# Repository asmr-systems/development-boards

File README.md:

# development-boards
development boards

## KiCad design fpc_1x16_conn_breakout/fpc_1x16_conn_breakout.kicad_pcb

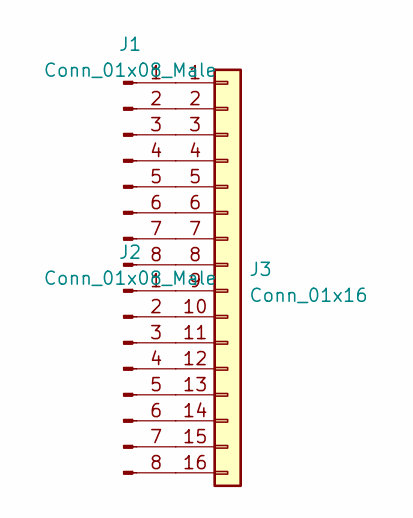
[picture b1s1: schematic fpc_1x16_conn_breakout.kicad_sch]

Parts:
J1, J2: Conn_01x08_Male; PinHeader_1x08_P2.54mm_Vertical
J3: Conn_01x16; Conn_FFC_1x16_0.5mm_TE_117347426

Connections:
unnamed: J1.1, J3.1
unnamed: J1.2, J3.2
unnamed: J1.3, J3.3
unnamed: J1.4, J3.4
unnamed: J1.5, J3.5
unnamed: J1.6, J3.6
unnamed: J1.7, J3.7
unnamed: J1.8, J3.8
unnamed: J2.1, J3.9
unnamed: J2.2, J3.10
unnamed: J2.3, J3.11
unnamed: J2.4, J3.12
unnamed: J2.5, J3.13
unnamed: J2.6, J3.14
unnamed: J2.7, J3.15
unnamed: J2.8, J3.16

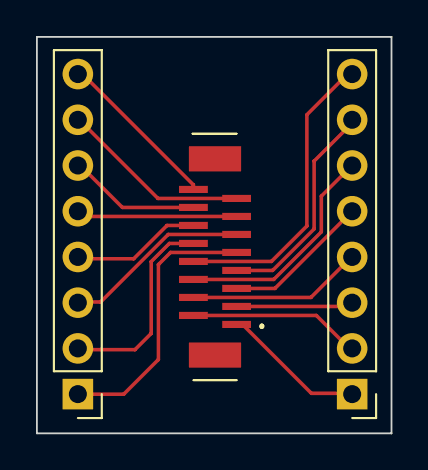
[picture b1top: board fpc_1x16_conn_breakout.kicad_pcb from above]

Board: 2 copper layers, 19.7 x 22.0 mm, 3 parts (0 on the bottom side), 16 nets.

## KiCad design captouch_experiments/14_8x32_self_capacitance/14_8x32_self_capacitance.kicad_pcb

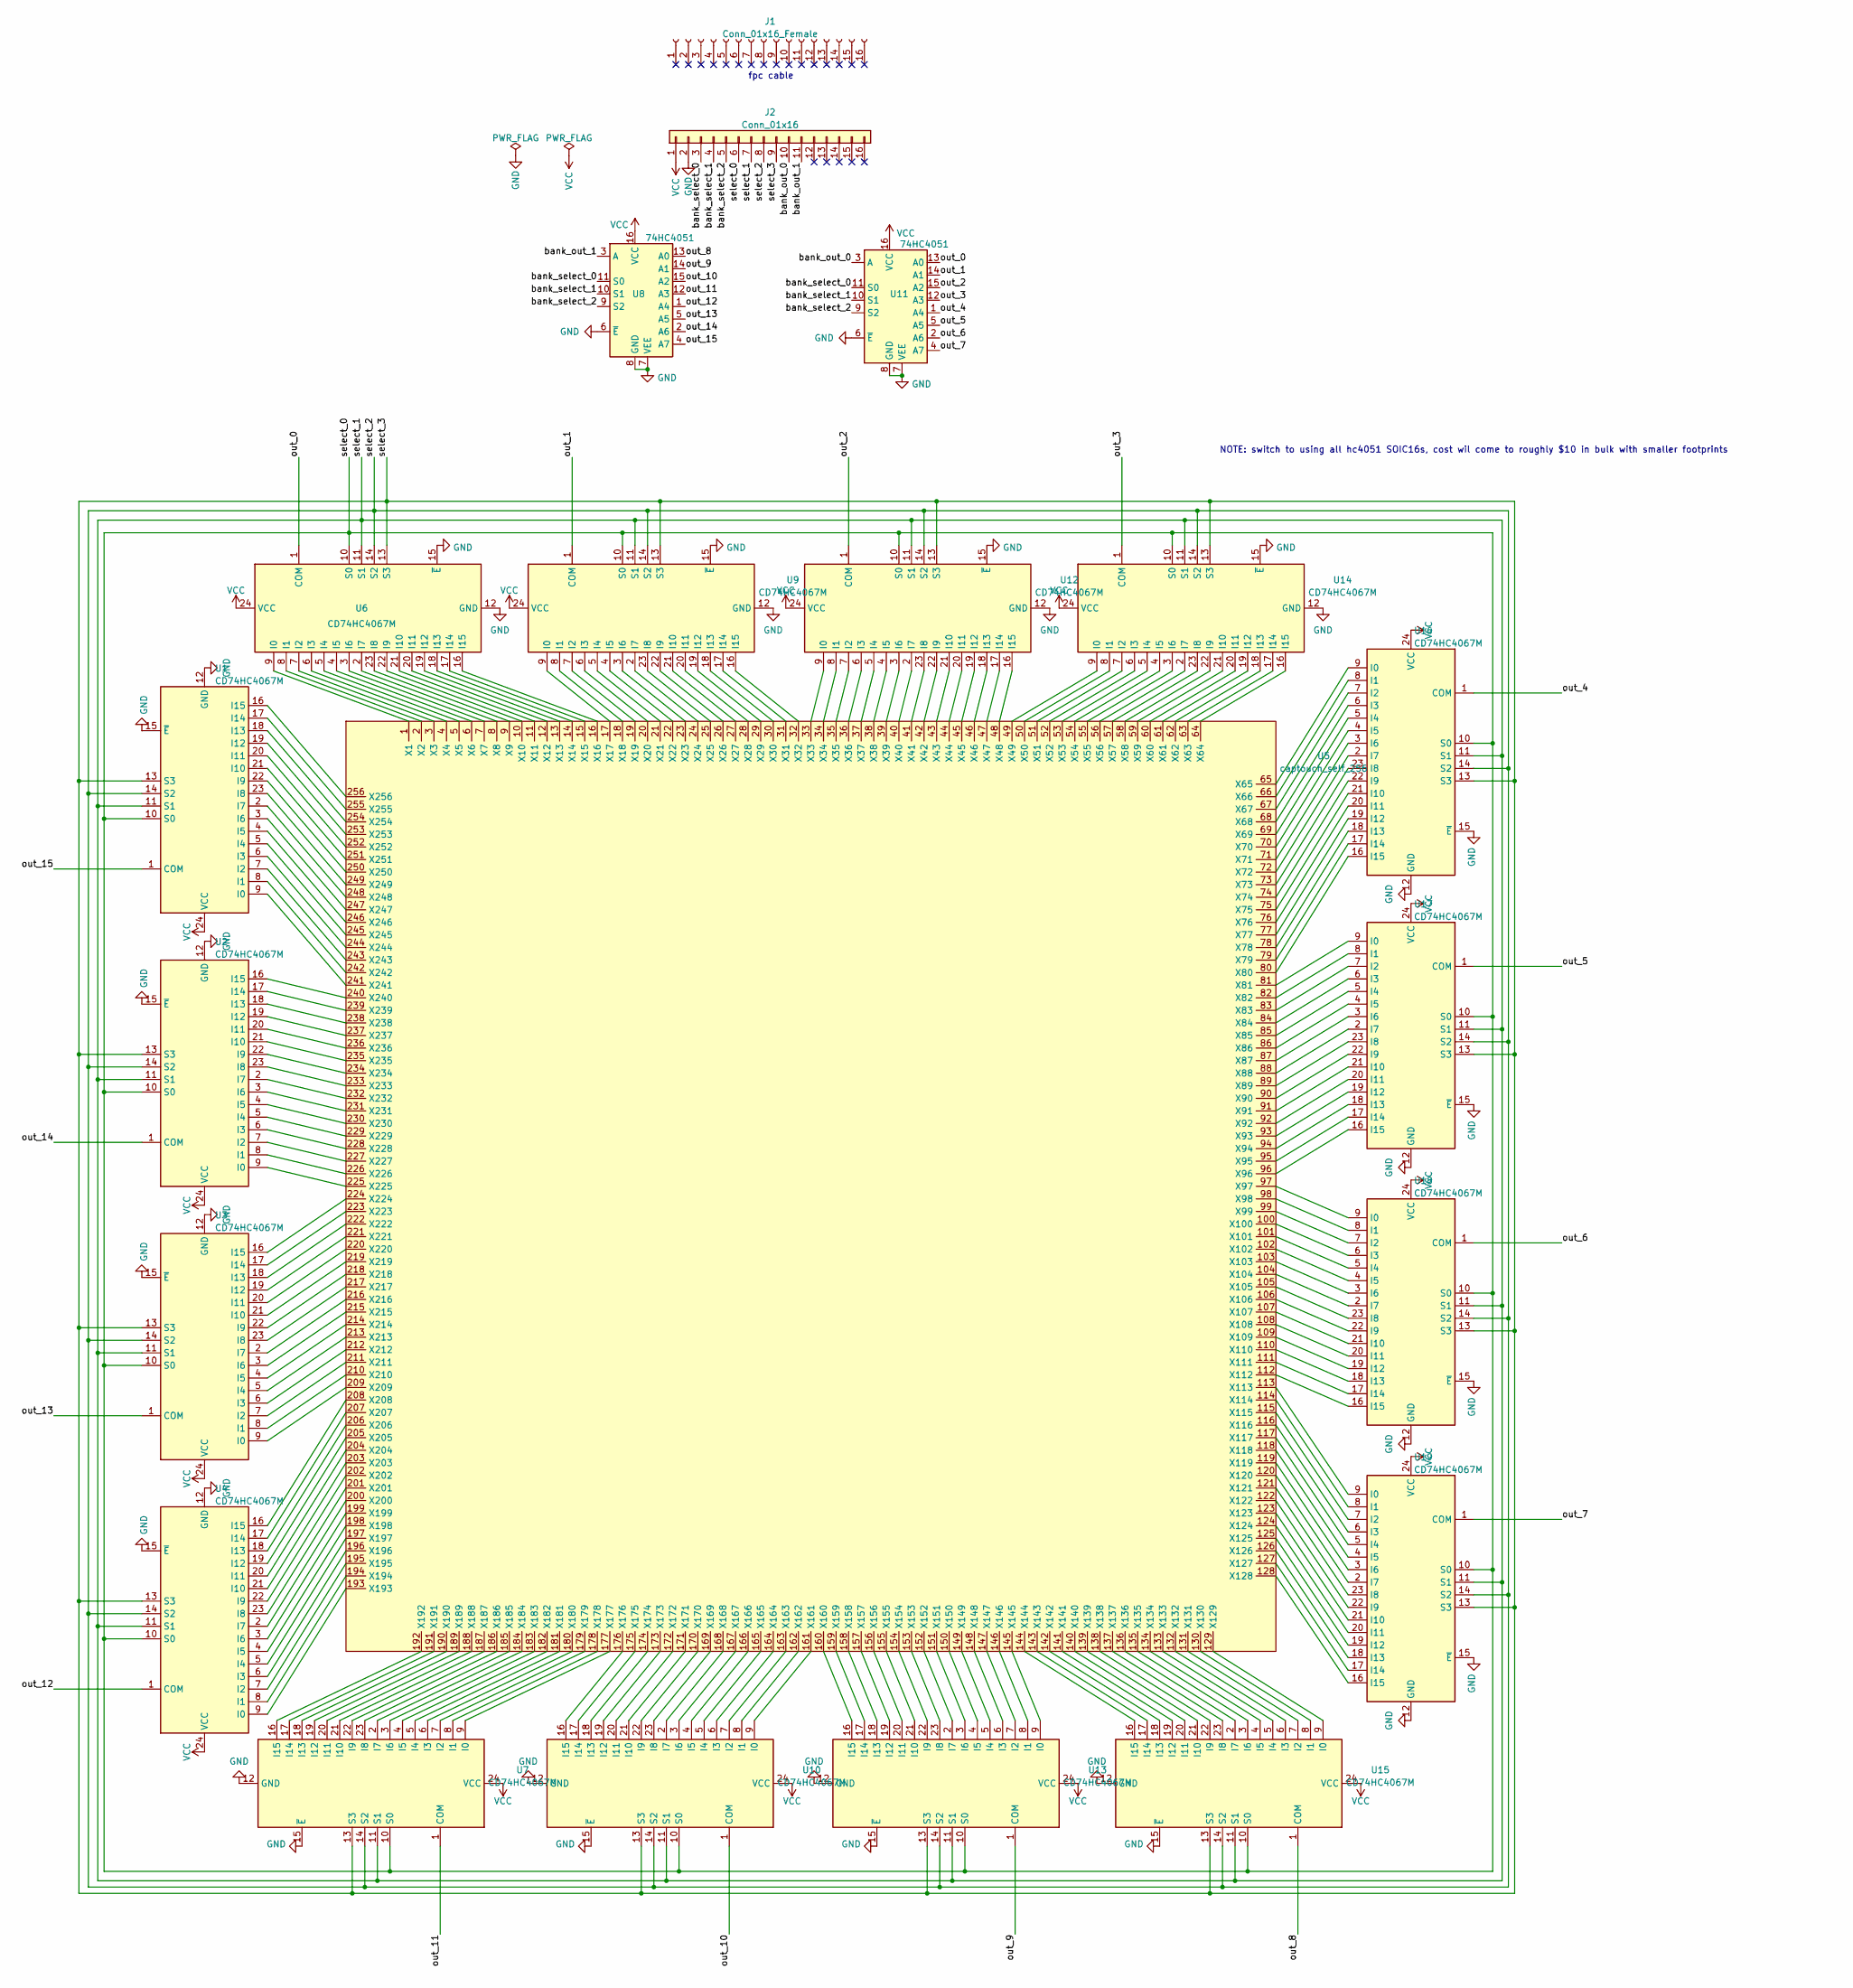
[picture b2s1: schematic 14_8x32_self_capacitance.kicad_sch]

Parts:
J1: Conn_01x16_Female; mpn 15166-0163
J2: Conn_01x16; Conn_FFC_1x16_0.5mm_TE_117347426; mpn 1-1734742-6
U1, U2, U3, U4, U6, U7, U9, U10, U12, U13, U14, U15, U16, U17, U18, U19: CD74HC4067M; SOIC-24W_7.5x15.4mm_P1.27mm; mpn CD74HC4067M
U5: captouch_self_256
U8, U11: 74HC4051; SOIC-16_3.9x9.9mm_P1.27mm; mpn 74HC4051D,653

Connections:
/bank_out_0: J2.10, U11.3 (A)
/bank_out_1: J2.11, U8.3 (A)
/bank_select_0: J2.3, U8.11 (S0), U11.11 (S0)
/bank_select_1: J2.4, U8.10 (S1), U11.10 (S1)
/bank_select_2: J2.5, U8.9 (S2), U11.9 (S2)
/out_0: U6.1 (COM), U11.13 (A0)
/out_1: U9.1 (COM), U11.14 (A1)
/out_2: U11.15 (A2), U12.1 (COM)
/out_3: U11.12 (A3), U14.1 (COM)
/out_4: U11.1 (A4), U16.1 (COM)
/out_5: U11.5 (A5), U17.1 (COM)
/out_6: U11.2 (A6), U18.1 (COM)
/out_7: U11.4 (A7), U19.1 (COM)
/out_8: U8.13 (A0), U15.1 (COM)
/out_9: U8.14 (A1), U13.1 (COM)
/out_10: U8.15 (A2), U10.1 (COM)
/out_11: U7.1 (COM), U8.12 (A3)
/out_12: U4.1 (COM), U8.1 (A4)
/out_13: U3.1 (COM), U8.5 (A5)
/out_14: U2.1 (COM), U8.2 (A6)
/out_15: U1.1 (COM), U8.4 (A7)
/select_0: J2.6, U1.10 (S0), U2.10 (S0), U3.10 (S0), U4.10 (S0), U6.10 (S0), U7.10 (S0), U9.10 (S0), U10.10 (S0), U12.10 (S0), U13.10 (S0), U14.10 (S0), U15.10 (S0), U16.10 (S0), U17.10 (S0), U18.10 (S0), U19.10 (S0)
/select_1: J2.7, U1.11 (S1), U2.11 (S1), U3.11 (S1), U4.11 (S1), U6.11 (S1), U7.11 (S1), U9.11 (S1), U10.11 (S1), U12.11 (S1), U13.11 (S1), U14.11 (S1), U15.11 (S1), U16.11 (S1), U17.11 (S1), U18.11 (S1), U19.11 (S1)
/select_2: J2.8, U1.14 (S2), U2.14 (S2), U3.14 (S2), U4.14 (S2), U6.14 (S2), U7.14 (S2), U9.14 (S2), U10.14 (S2), U12.14 (S2), U13.14 (S2), U14.14 (S2), U15.14 (S2), U16.14 (S2), U17.14 (S2), U18.14 (S2), U19.14 (S2)
/select_3: J2.9, U1.13 (S3), U2.13 (S3), U3.13 (S3), U4.13 (S3), U6.13 (S3), U7.13 (S3), U9.13 (S3), U10.13 (S3), U12.13 (S3), U13.13 (S3), U14.13 (S3), U15.13 (S3), U16.13 (S3), U17.13 (S3), U18.13 (S3), U19.13 (S3)
GND: J2.2, U1.12 (GND), U1.15 (~E), U2.12 (GND), U2.15 (~E), U3.12 (GND), U3.15 (~E), U4.12 (GND), U4.15 (~E), U6.12 (GND), U6.15 (~E), U7.12 (GND), U7.15 (~E), U8.6 (~E), U8.7 (VEE), U8.8 (GND), U9.12 (GND), U9.15 (~E), U10.12 (GND), U10.15 (~E), U11.6 (~E), U11.7 (VEE), U11.8 (GND), U12.12 (GND), U12.15 (~E), U13.12 (GND), U13.15 (~E), U14.12 (GND), U14.15 (~E), U15.12 (GND), U15.15 (~E), U16.12 (GND), U16.15 (~E), U17.12 (GND), U17.15 (~E), U18.12 (GND), U18.15 (~E), U19.12 (GND), U19.15 (~E)
unnamed: U1.2 (I7), U5.248 (X248)
unnamed: U1.3 (I6), U5.247 (X247)
unnamed: U1.4 (I5), U5.246 (X246)
unnamed: U1.5 (I4), U5.245 (X245)
unnamed: U1.6 (I3), U5.244 (X244)
unnamed: U1.7 (I2), U5.243 (X243)
unnamed: U1.8 (I1), U5.242 (X242)
unnamed: U1.9 (I0), U5.241 (X241)
unnamed: U1.16 (I15), U5.256 (X256)
unnamed: U1.17 (I14), U5.255 (X255)
unnamed: U1.18 (I13), U5.254 (X254)
unnamed: U1.19 (I12), U5.253 (X253)
unnamed: U1.20 (I11), U5.252 (X252)
unnamed: U1.21 (I10), U5.251 (X251)
unnamed: U1.22 (I9), U5.250 (X250)
unnamed: U1.23 (I8), U5.249 (X249)
unnamed: U2.2 (I7), U5.232 (X232)
unnamed: U2.3 (I6), U5.231 (X231)
unnamed: U2.4 (I5), U5.230 (X230)
unnamed: U2.5 (I4), U5.229 (X229)
unnamed: U2.6 (I3), U5.228 (X228)
unnamed: U2.7 (I2), U5.227 (X227)
unnamed: U2.8 (I1), U5.226 (X226)
unnamed: U2.9 (I0), U5.225 (X225)
unnamed: U2.16 (I15), U5.240 (X240)
unnamed: U2.17 (I14), U5.239 (X239)
unnamed: U2.18 (I13), U5.238 (X238)
unnamed: U2.19 (I12), U5.237 (X237)
unnamed: U2.20 (I11), U5.236 (X236)
unnamed: U2.21 (I10), U5.235 (X235)
unnamed: U2.22 (I9), U5.234 (X234)
unnamed: U2.23 (I8), U5.233 (X233)
unnamed: U3.2 (I7), U5.216 (X216)
unnamed: U3.3 (I6), U5.215 (X215)
unnamed: U3.4 (I5), U5.214 (X214)
unnamed: U3.5 (I4), U5.213 (X213)
unnamed: U3.6 (I3), U5.212 (X212)
unnamed: U3.7 (I2), U5.211 (X211)
unnamed: U3.8 (I1), U5.210 (X210)
unnamed: U3.9 (I0), U5.209 (X209)
unnamed: U3.16 (I15), U5.224 (X224)
unnamed: U3.17 (I14), U5.223 (X223)
unnamed: U3.18 (I13), U5.222 (X222)
unnamed: U3.19 (I12), U5.221 (X221)
unnamed: U3.20 (I11), U5.220 (X220)
unnamed: U3.21 (I10), U5.219 (X219)
unnamed: U3.22 (I9), U5.218 (X218)
unnamed: U3.23 (I8), U5.217 (X217)
unnamed: U4.2 (I7), U5.200 (X200)
unnamed: U4.3 (I6), U5.199 (X199)
unnamed: U4.4 (I5), U5.198 (X198)
unnamed: U4.5 (I4), U5.197 (X197)
unnamed: U4.6 (I3), U5.196 (X196)
unnamed: U4.7 (I2), U5.195 (X195)
unnamed: U4.8 (I1), U5.194 (X194)
unnamed: U4.9 (I0), U5.193 (X193)
unnamed: U4.16 (I15), U5.208 (X208)
unnamed: U4.17 (I14), U5.207 (X207)
unnamed: U4.18 (I13), U5.206 (X206)
unnamed: U4.19 (I12), U5.205 (X205)
unnamed: U4.20 (I11), U5.204 (X204)
unnamed: U4.21 (I10), U5.203 (X203)
unnamed: U4.22 (I9), U5.202 (X202)
unnamed: U4.23 (I8), U5.201 (X201)
unnamed: U5.1 (X1), U6.9 (I0)
unnamed: U5.2 (X2), U6.8 (I1)
unnamed: U5.3 (X3), U6.7 (I2)
unnamed: U5.4 (X4), U6.6 (I3)
unnamed: U5.5 (X5), U6.5 (I4)
unnamed: U5.6 (X6), U6.4 (I5)
unnamed: U5.7 (X7), U6.3 (I6)
unnamed: U5.8 (X8), U6.2 (I7)
unnamed: U5.9 (X9), U6.23 (I8)
unnamed: U5.10 (X10), U6.22 (I9)
unnamed: U5.11 (X11), U6.21 (I10)
unnamed: U5.12 (X12), U6.20 (I11)
unnamed: U5.13 (X13), U6.19 (I12)
unnamed: U5.14 (X14), U6.18 (I13)
unnamed: U5.15 (X15), U6.17 (I14)
unnamed: U5.16 (X16), U6.16 (I15)
unnamed: U5.17 (X17), U9.9 (I0)
unnamed: U5.18 (X18), U9.8 (I1)
unnamed: U5.19 (X19), U9.7 (I2)
unnamed: U5.20 (X20), U9.6 (I3)
unnamed: U5.21 (X21), U9.5 (I4)
unnamed: U5.22 (X22), U9.4 (I5)
unnamed: U5.23 (X23), U9.3 (I6)
unnamed: U5.24 (X24), U9.2 (I7)
unnamed: U5.25 (X25), U9.23 (I8)
unnamed: U5.26 (X26), U9.22 (I9)
unnamed: U5.27 (X27), U9.21 (I10)
unnamed: U5.28 (X28), U9.20 (I11)
unnamed: U5.29 (X29), U9.19 (I12)
unnamed: U5.30 (X30), U9.18 (I13)
unnamed: U5.31 (X31), U9.17 (I14)
unnamed: U5.32 (X32), U9.16 (I15)
unnamed: U5.177 (X177), U7.9 (I0)
unnamed: U5.178 (X178), U7.8 (I1)
unnamed: U5.179 (X179), U7.7 (I2)
unnamed: U5.180 (X180), U7.6 (I3)
unnamed: U5.181 (X181), U7.5 (I4)
unnamed: U5.182 (X182), U7.4 (I5)
unnamed: U5.183 (X183), U7.3 (I6)
unnamed: U5.184 (X184), U7.2 (I7)
unnamed: U5.185 (X185), U7.23 (I8)
unnamed: U5.186 (X186), U7.22 (I9)
unnamed: U5.187 (X187), U7.21 (I10)
unnamed: U5.188 (X188), U7.20 (I11)
unnamed: U5.189 (X189), U7.19 (I12)
unnamed: U5.190 (X190), U7.18 (I13)
unnamed: U5.191 (X191), U7.17 (I14)
unnamed: U5.192 (X192), U7.16 (I15)
unnamed: U5.168 (X168), U10.2 (I7)
unnamed: U5.167 (X167), U10.3 (I6)
unnamed: U5.166 (X166), U10.4 (I5)
unnamed: U5.165 (X165), U10.5 (I4)
unnamed: U5.164 (X164), U10.6 (I3)
unnamed: U5.163 (X163), U10.7 (I2)
unnamed: U5.162 (X162), U10.8 (I1)
unnamed: U5.161 (X161), U10.9 (I0)
unnamed: U5.176 (X176), U10.16 (I15)
unnamed: U5.175 (X175), U10.17 (I14)
unnamed: U5.174 (X174), U10.18 (I13)
unnamed: U5.173 (X173), U10.19 (I12)
unnamed: U5.172 (X172), U10.20 (I11)
unnamed: U5.171 (X171), U10.21 (I10)
unnamed: U5.170 (X170), U10.22 (I9)
unnamed: U5.169 (X169), U10.23 (I8)
unnamed: U5.40 (X40), U12.2 (I7)
unnamed: U5.39 (X39), U12.3 (I6)
unnamed: U5.38 (X38), U12.4 (I5)
unnamed: U5.37 (X37), U12.5 (I4)
unnamed: U5.36 (X36), U12.6 (I3)
unnamed: U5.35 (X35), U12.7 (I2)
unnamed: U5.34 (X34), U12.8 (I1)
unnamed: U5.33 (X33), U12.9 (I0)
unnamed: U5.48 (X48), U12.16 (I15)
unnamed: U5.47 (X47), U12.17 (I14)
unnamed: U5.46 (X46), U12.18 (I13)
unnamed: U5.45 (X45), U12.19 (I12)
unnamed: U5.44 (X44), U12.20 (I11)
unnamed: U5.43 (X43), U12.21 (I10)
unnamed: U5.42 (X42), U12.22 (I9)
unnamed: U5.41 (X41), U12.23 (I8)
unnamed: U5.152 (X152), U13.2 (I7)
unnamed: U5.151 (X151), U13.3 (I6)
unnamed: U5.150 (X150), U13.4 (I5)
unnamed: U5.149 (X149), U13.5 (I4)
unnamed: U5.148 (X148), U13.6 (I3)
unnamed: U5.147 (X147), U13.7 (I2)
unnamed: U5.146 (X146), U13.8 (I1)
unnamed: U5.145 (X145), U13.9 (I0)
unnamed: U5.160 (X160), U13.16 (I15)
unnamed: U5.159 (X159), U13.17 (I14)
unnamed: U5.158 (X158), U13.18 (I13)
unnamed: U5.157 (X157), U13.19 (I12)
unnamed: U5.156 (X156), U13.20 (I11)
unnamed: U5.155 (X155), U13.21 (I10)
unnamed: U5.154 (X154), U13.22 (I9)
unnamed: U5.153 (X153), U13.23 (I8)
unnamed: U5.56 (X56), U14.2 (I7)
unnamed: U5.55 (X55), U14.3 (I6)
unnamed: U5.54 (X54), U14.4 (I5)
unnamed: U5.53 (X53), U14.5 (I4)
unnamed: U5.52 (X52), U14.6 (I3)
unnamed: U5.51 (X51), U14.7 (I2)
unnamed: U5.50 (X50), U14.8 (I1)
unnamed: U5.49 (X49), U14.9 (I0)
unnamed: U5.64 (X64), U14.16 (I15)
unnamed: U5.63 (X63), U14.17 (I14)
unnamed: U5.62 (X62), U14.18 (I13)
unnamed: U5.61 (X61), U14.19 (I12)
unnamed: U5.60 (X60), U14.20 (I11)
unnamed: U5.59 (X59), U14.21 (I10)
unnamed: U5.58 (X58), U14.22 (I9)
unnamed: U5.57 (X57), U14.23 (I8)
unnamed: U5.136 (X136), U15.2 (I7)
unnamed: U5.135 (X135), U15.3 (I6)
unnamed: U5.134 (X134), U15.4 (I5)
unnamed: U5.133 (X133), U15.5 (I4)
unnamed: U5.132 (X132), U15.6 (I3)
unnamed: U5.131 (X131), U15.7 (I2)
unnamed: U5.130 (X130), U15.8 (I1)
unnamed: U5.129 (X129), U15.9 (I0)
unnamed: U5.144 (X144), U15.16 (I15)
unnamed: U5.143 (X143), U15.17 (I14)
unnamed: U5.142 (X142), U15.18 (I13)
unnamed: U5.141 (X141), U15.19 (I12)
unnamed: U5.140 (X140), U15.20 (I11)
unnamed: U5.139 (X139), U15.21 (I10)
unnamed: U5.138 (X138), U15.22 (I9)
unnamed: U5.137 (X137), U15.23 (I8)
unnamed: U5.72 (X72), U16.2 (I7)
unnamed: U5.71 (X71), U16.3 (I6)
unnamed: U5.70 (X70), U16.4 (I5)
unnamed: U5.69 (X69), U16.5 (I4)
unnamed: U5.68 (X68), U16.6 (I3)
unnamed: U5.67 (X67), U16.7 (I2)
unnamed: U5.66 (X66), U16.8 (I1)
unnamed: U5.65 (X65), U16.9 (I0)
unnamed: U5.80 (X80), U16.16 (I15)
unnamed: U5.79 (X79), U16.17 (I14)
unnamed: U5.78 (X78), U16.18 (I13)
unnamed: U5.77 (X77), U16.19 (I12)
unnamed: U5.76 (X76), U16.20 (I11)
unnamed: U5.75 (X75), U16.21 (I10)
unnamed: U5.74 (X74), U16.22 (I9)
unnamed: U5.73 (X73), U16.23 (I8)
unnamed: U5.88 (X88), U17.2 (I7)
unnamed: U5.87 (X87), U17.3 (I6)
unnamed: U5.86 (X86), U17.4 (I5)
unnamed: U5.85 (X85), U17.5 (I4)
unnamed: U5.84 (X84), U17.6 (I3)
unnamed: U5.83 (X83), U17.7 (I2)
unnamed: U5.82 (X82), U17.8 (I1)
unnamed: U5.81 (X81), U17.9 (I0)
unnamed: U5.96 (X96), U17.16 (I15)
unnamed: U5.95 (X95), U17.17 (I14)
unnamed: U5.94 (X94), U17.18 (I13)
unnamed: U5.93 (X93), U17.19 (I12)
unnamed: U5.92 (X92), U17.20 (I11)
unnamed: U5.91 (X91), U17.21 (I10)
unnamed: U5.90 (X90), U17.22 (I9)
unnamed: U5.89 (X89), U17.23 (I8)
unnamed: U5.104 (X104), U18.2 (I7)
unnamed: U5.103 (X103), U18.3 (I6)
unnamed: U5.102 (X102), U18.4 (I5)
unnamed: U5.101 (X101), U18.5 (I4)
unnamed: U5.100 (X100), U18.6 (I3)
unnamed: U5.99 (X99), U18.7 (I2)
unnamed: U5.98 (X98), U18.8 (I1)
unnamed: U5.97 (X97), U18.9 (I0)
unnamed: U5.112 (X112), U18.16 (I15)
unnamed: U5.111 (X111), U18.17 (I14)
unnamed: U5.110 (X110), U18.18 (I13)
unnamed: U5.109 (X109), U18.19 (I12)
unnamed: U5.108 (X108), U18.20 (I11)
unnamed: U5.107 (X107), U18.21 (I10)
unnamed: U5.106 (X106), U18.22 (I9)
unnamed: U5.105 (X105), U18.23 (I8)
unnamed: U5.120 (X120), U19.2 (I7)
unnamed: U5.119 (X119), U19.3 (I6)
unnamed: U5.118 (X118), U19.4 (I5)
unnamed: U5.117 (X117), U19.5 (I4)
unnamed: U5.116 (X116), U19.6 (I3)
unnamed: U5.115 (X115), U19.7 (I2)
unnamed: U5.114 (X114), U19.8 (I1)
unnamed: U5.113 (X113), U19.9 (I0)
unnamed: U5.128 (X128), U19.16 (I15)
unnamed: U5.127 (X127), U19.17 (I14)
unnamed: U5.126 (X126), U19.18 (I13)
unnamed: U5.125 (X125), U19.19 (I12)
unnamed: U5.124 (X124), U19.20 (I11)
unnamed: U5.123 (X123), U19.21 (I10)
unnamed: U5.122 (X122), U19.22 (I9)
unnamed: U5.121 (X121), U19.23 (I8)
VCC: J2.1, U1.24 (VCC), U2.24 (VCC), U3.24 (VCC), U4.24 (VCC), U6.24 (VCC), U7.24 (VCC), U8.16 (VCC), U9.24 (VCC), U10.24 (VCC), U11.16 (VCC), U12.24 (VCC), U13.24 (VCC), U14.24 (VCC), U15.24 (VCC), U16.24 (VCC), U17.24 (VCC), U18.24 (VCC), U19.24 (VCC)

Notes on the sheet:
fpc cable
NOTE: switch to using all hc4051 SOIC16s, cost wil come to roughly $10 in bulk with smaller footprints

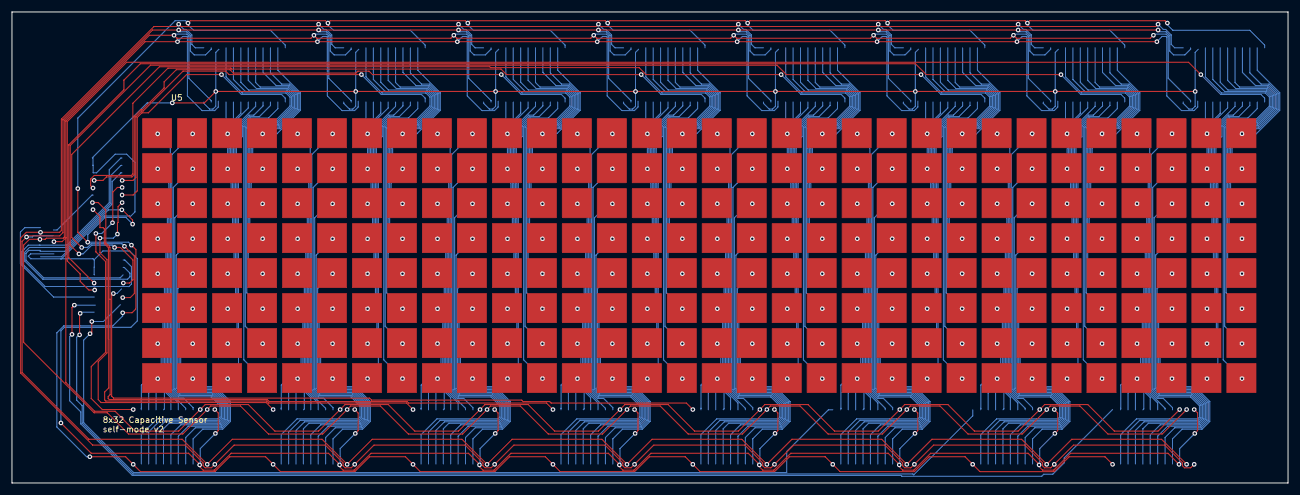
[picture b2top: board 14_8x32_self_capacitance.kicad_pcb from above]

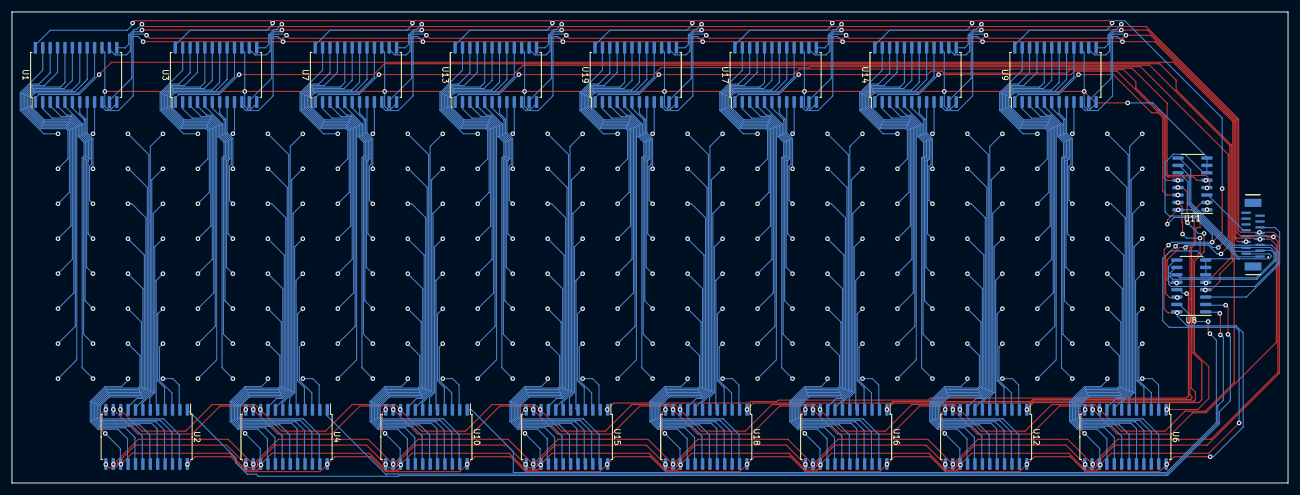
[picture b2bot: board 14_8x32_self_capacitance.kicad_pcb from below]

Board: 2 copper layers, 218.9 x 80.8 mm, 20 parts (19 on the bottom side), 283 nets.

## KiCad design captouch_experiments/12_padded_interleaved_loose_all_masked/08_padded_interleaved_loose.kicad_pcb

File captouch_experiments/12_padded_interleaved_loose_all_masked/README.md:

``` shell
asmr design touch-grid -f test.svg -x 32 -y 8 -s 0.4 --pitch 6 --xwidth 0.4 --ywidth 0.4 --color -p interleaved --padding 1
```

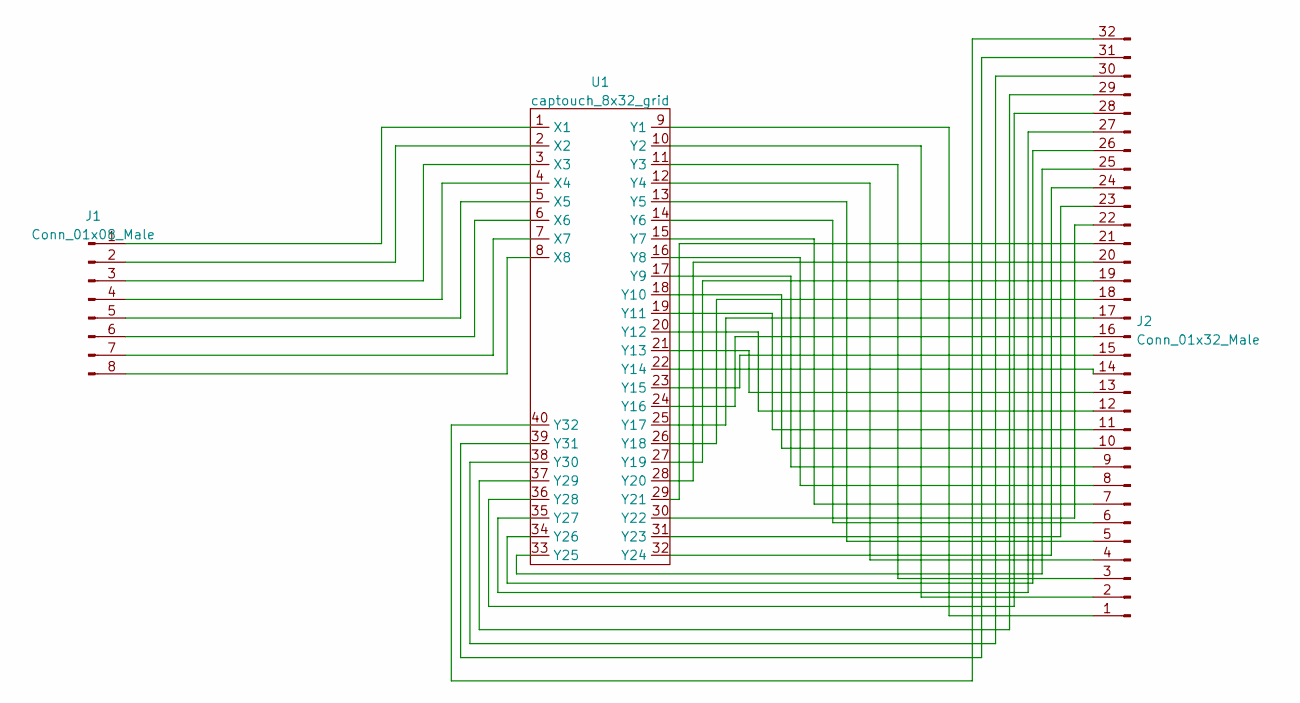
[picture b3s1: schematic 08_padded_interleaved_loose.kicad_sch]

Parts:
J1: Conn_01x08_Male; Conn_FFC_1x8_0.5mm_Molex_5019510830
J2: Conn_01x32_Male; Conn_FFC_1x32_0.5mm_Molex_5019513210
U1: captouch_8x32_grid; captouch_8x32_padded_interleaved_loose_all_masked

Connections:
unnamed: J1.1, U1.1 (X1)
unnamed: J1.2, U1.2 (X2)
unnamed: J1.3, U1.3 (X3)
unnamed: J1.4, U1.4 (X4)
unnamed: J1.5, U1.5 (X5)
unnamed: J1.6, U1.6 (X6)
unnamed: J1.7, U1.7 (X7)
unnamed: J1.8, U1.8 (X8)
unnamed: J2.1, U1.9 (Y1)
unnamed: J2.2, U1.10 (Y2)
unnamed: J2.3, U1.11 (Y3)
unnamed: J2.4, U1.12 (Y4)
unnamed: J2.5, U1.13 (Y5)
unnamed: J2.6, U1.14 (Y6)
unnamed: J2.7, U1.15 (Y7)
unnamed: J2.8, U1.16 (Y8)
unnamed: J2.9, U1.17 (Y9)
unnamed: J2.10, U1.18 (Y10)
unnamed: J2.11, U1.19 (Y11)
unnamed: J2.12, U1.20 (Y12)
unnamed: J2.13, U1.21 (Y13)
unnamed: J2.14, U1.22 (Y14)
unnamed: J2.15, U1.23 (Y15)
unnamed: J2.16, U1.24 (Y16)
unnamed: J2.17, U1.25 (Y17)
unnamed: J2.18, U1.26 (Y18)
unnamed: J2.19, U1.27 (Y19)
unnamed: J2.20, U1.28 (Y20)
unnamed: J2.21, U1.29 (Y21)
unnamed: J2.22, U1.30 (Y22)
unnamed: J2.23, U1.31 (Y23)
unnamed: J2.24, U1.32 (Y24)
unnamed: J2.25, U1.33 (Y25)
unnamed: J2.26, U1.34 (Y26)
unnamed: J2.27, U1.35 (Y27)
unnamed: J2.28, U1.36 (Y28)
unnamed: J2.29, U1.37 (Y29)
unnamed: J2.30, U1.38 (Y30)
unnamed: J2.31, U1.39 (Y31)
unnamed: J2.32, U1.40 (Y32)

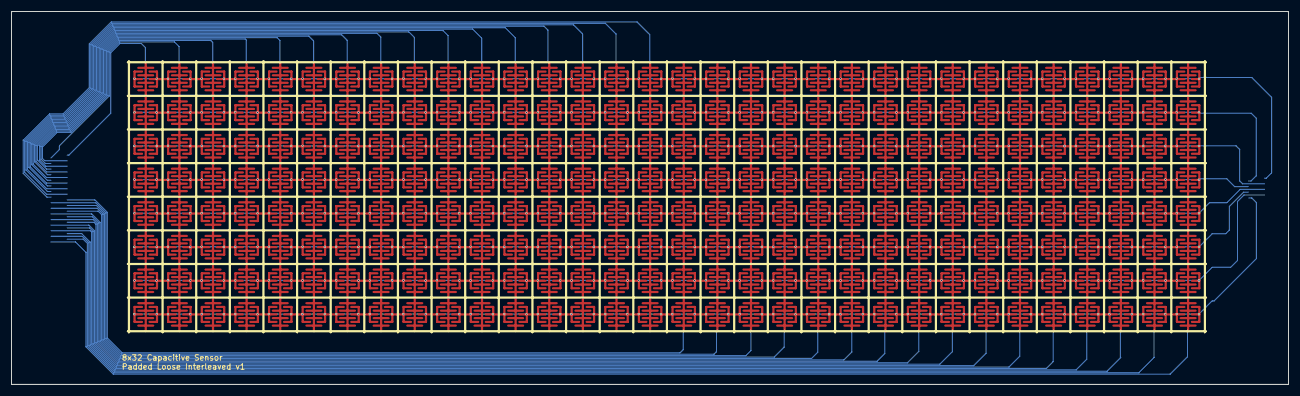
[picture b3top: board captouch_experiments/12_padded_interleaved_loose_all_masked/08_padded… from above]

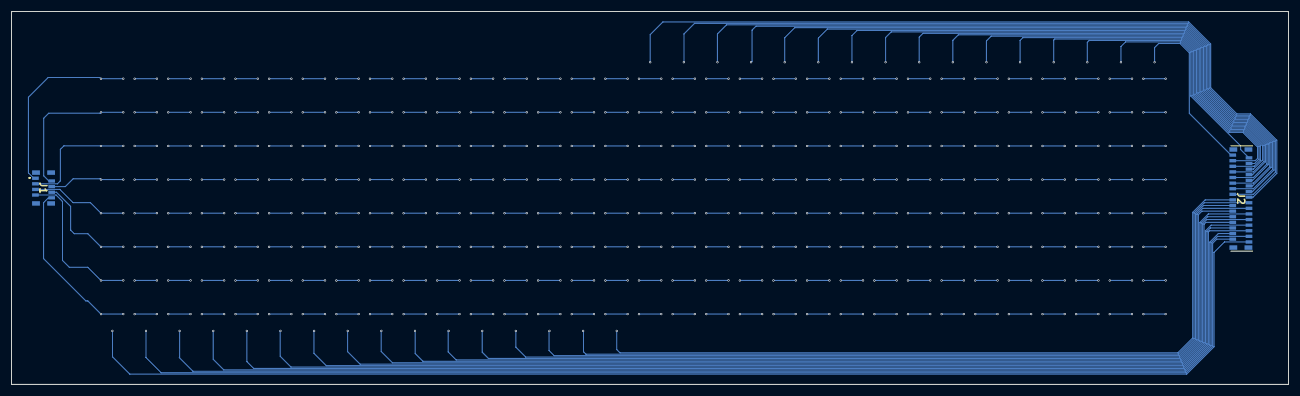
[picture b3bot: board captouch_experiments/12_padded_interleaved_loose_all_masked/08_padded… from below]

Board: 2 copper layers, 227.9 x 66.5 mm, 3 parts (2 on the bottom side), 40 nets.

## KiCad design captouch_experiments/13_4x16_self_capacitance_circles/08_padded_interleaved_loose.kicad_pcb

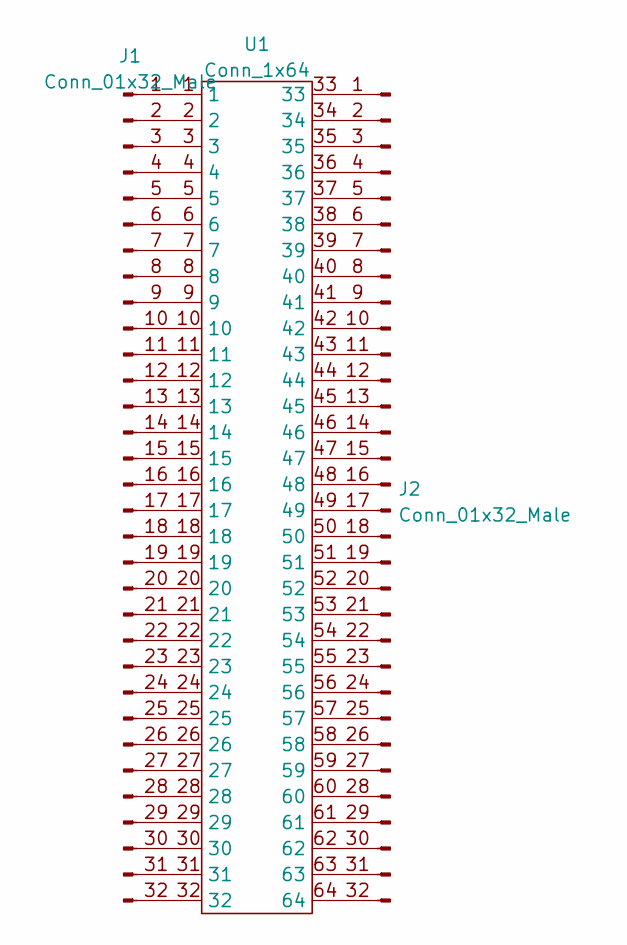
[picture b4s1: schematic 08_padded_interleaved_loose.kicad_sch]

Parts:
J1, J2: Conn_01x32_Male; Conn_FFC_1x32_0.5mm_Molex_5019513210
U1: Conn_1x64; captouch_4x16_self_cap_circles

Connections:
unnamed: J1.1, U1.1
unnamed: J1.2, U1.2
unnamed: J1.3, U1.3
unnamed: J1.4, U1.4
unnamed: J1.5, U1.5
unnamed: J1.6, U1.6
unnamed: J1.7, U1.7
unnamed: J1.8, U1.8
unnamed: J1.9, U1.9
unnamed: J1.10, U1.10
unnamed: J1.11, U1.11
unnamed: J1.12, U1.12
unnamed: J1.13, U1.13
unnamed: J1.14, U1.14
unnamed: J1.15, U1.15
unnamed: J1.16, U1.16
unnamed: J1.17, U1.17
unnamed: J1.18, U1.18
unnamed: J1.19, U1.19
unnamed: J1.20, U1.20
unnamed: J1.21, U1.21
unnamed: J1.22, U1.22
unnamed: J1.23, U1.23
unnamed: J1.24, U1.24
unnamed: J1.25, U1.25
unnamed: J1.26, U1.26
unnamed: J1.27, U1.27
unnamed: J1.28, U1.28
unnamed: J1.29, U1.29
unnamed: J1.30, U1.30
unnamed: J1.31, U1.31
unnamed: J1.32, U1.32
unnamed: J2.1, U1.33
unnamed: J2.2, U1.34
unnamed: J2.3, U1.35
unnamed: J2.4, U1.36
unnamed: J2.5, U1.37
unnamed: J2.6, U1.38
unnamed: J2.7, U1.39
unnamed: J2.8, U1.40
unnamed: J2.9, U1.41
unnamed: J2.10, U1.42
unnamed: J2.11, U1.43
unnamed: J2.12, U1.44
unnamed: J2.13, U1.45
unnamed: J2.14, U1.46
unnamed: J2.15, U1.47
unnamed: J2.16, U1.48
unnamed: J2.17, U1.49
unnamed: J2.18, U1.50
unnamed: J2.19, U1.51
unnamed: J2.20, U1.52
unnamed: J2.21, U1.53
unnamed: J2.22, U1.54
unnamed: J2.23, U1.55
unnamed: J2.24, U1.56
unnamed: J2.25, U1.57
unnamed: J2.26, U1.58
unnamed: J2.27, U1.59
unnamed: J2.28, U1.60
unnamed: J2.29, U1.61
unnamed: J2.30, U1.62
unnamed: J2.31, U1.63
unnamed: J2.32, U1.64

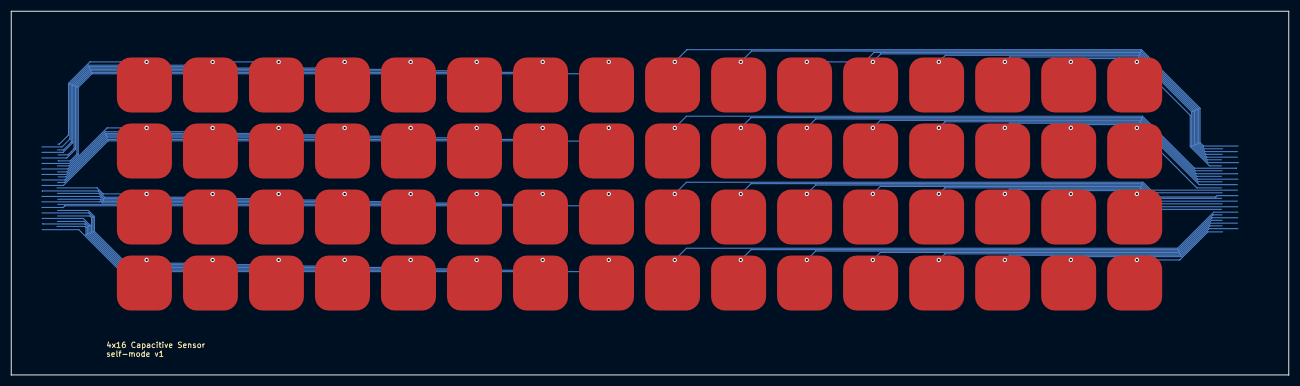
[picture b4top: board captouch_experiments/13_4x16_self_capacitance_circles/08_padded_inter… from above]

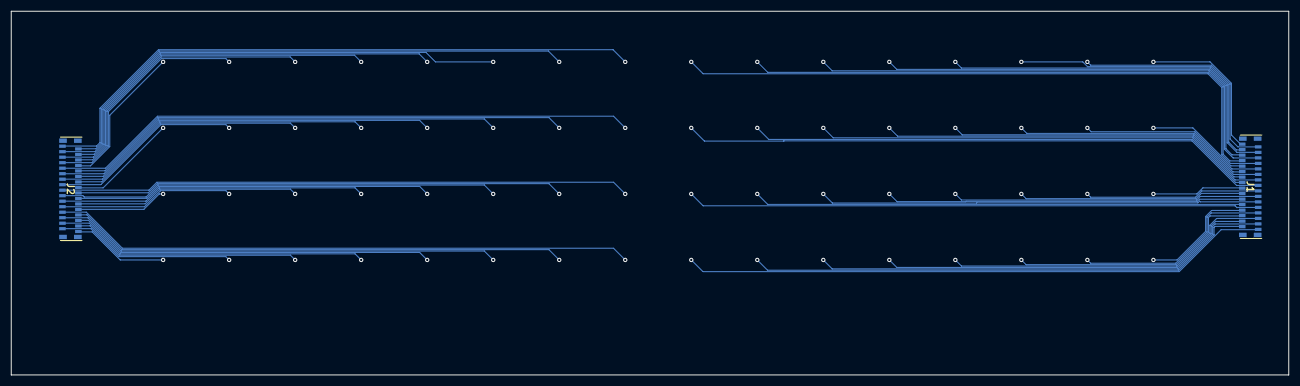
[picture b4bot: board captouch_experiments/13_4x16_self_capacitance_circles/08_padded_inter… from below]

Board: 2 copper layers, 232.2 x 66.1 mm, 3 parts (2 on the bottom side), 64 nets.

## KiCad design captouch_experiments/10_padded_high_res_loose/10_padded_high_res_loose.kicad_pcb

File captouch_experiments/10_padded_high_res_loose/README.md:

``` shell
asmr design touch-grid -f padded_high_res_loose.svg -x 64 -y 16 --pitch 3 --xwidth 0.127 --ywidth 0.127 --separation 0.2 --padding 0.6 --silk_scaling 2 2 --color
```

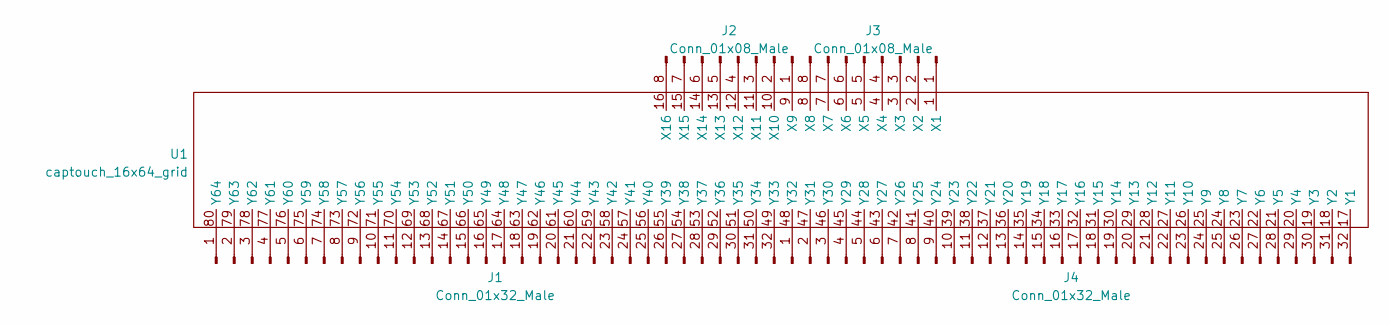
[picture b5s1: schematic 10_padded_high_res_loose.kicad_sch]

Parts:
J1, J4: Conn_01x32_Male; Conn_FFC_1x32_0.5mm_Molex_5019513210
J2, J3: Conn_01x08_Male; Conn_FFC_1x8_0.5mm_Molex_5019510830
U1: captouch_16x64_grid; captouch_16x64_padded_interleaved_loose

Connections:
unnamed: J1.1, U1.80 (Y64)
unnamed: J1.2, U1.79 (Y63)
unnamed: J1.3, U1.78 (Y62)
unnamed: J1.4, U1.77 (Y61)
unnamed: J1.5, U1.76 (Y60)
unnamed: J1.6, U1.75 (Y59)
unnamed: J1.7, U1.74 (Y58)
unnamed: J1.8, U1.73 (Y57)
unnamed: J1.9, U1.72 (Y56)
unnamed: J1.10, U1.71 (Y55)
unnamed: J1.11, U1.70 (Y54)
unnamed: J1.12, U1.69 (Y53)
unnamed: J1.13, U1.68 (Y52)
unnamed: J1.14, U1.67 (Y51)
unnamed: J1.15, U1.66 (Y50)
unnamed: J1.16, U1.65 (Y49)
unnamed: J1.17, U1.64 (Y48)
unnamed: J1.18, U1.63 (Y47)
unnamed: J1.19, U1.62 (Y46)
unnamed: J1.20, U1.61 (Y45)
unnamed: J1.21, U1.60 (Y44)
unnamed: J1.22, U1.59 (Y43)
unnamed: J1.23, U1.58 (Y42)
unnamed: J1.24, U1.57 (Y41)
unnamed: J1.25, U1.56 (Y40)
unnamed: J1.26, U1.55 (Y39)
unnamed: J1.27, U1.54 (Y38)
unnamed: J1.28, U1.53 (Y37)
unnamed: J1.29, U1.52 (Y36)
unnamed: J1.30, U1.51 (Y35)
unnamed: J1.31, U1.50 (Y34)
unnamed: J1.32, U1.49 (Y33)
unnamed: J2.1, U1.9 (X9)
unnamed: J2.2, U1.10 (X10)
unnamed: J2.3, U1.11 (X11)
unnamed: J2.4, U1.12 (X12)
unnamed: J2.5, U1.13 (X13)
unnamed: J2.6, U1.14 (X14)
unnamed: J2.7, U1.15 (X15)
unnamed: J2.8, U1.16 (X16)
unnamed: J3.1, U1.1 (X1)
unnamed: J3.2, U1.2 (X2)
unnamed: J3.3, U1.3 (X3)
unnamed: J3.4, U1.4 (X4)
unnamed: J3.5, U1.5 (X5)
unnamed: J3.6, U1.6 (X6)
unnamed: J3.7, U1.7 (X7)
unnamed: J3.8, U1.8 (X8)
unnamed: J4.1, U1.48 (Y32)
unnamed: J4.2, U1.47 (Y31)
unnamed: J4.3, U1.46 (Y30)
unnamed: J4.4, U1.45 (Y29)
unnamed: J4.5, U1.44 (Y28)
unnamed: J4.6, U1.43 (Y27)
unnamed: J4.7, U1.42 (Y26)
unnamed: J4.8, U1.41 (Y25)
unnamed: J4.9, U1.40 (Y24)
unnamed: J4.10, U1.39 (Y23)
unnamed: J4.11, U1.38 (Y22)
unnamed: J4.12, U1.37 (Y21)
unnamed: J4.13, U1.36 (Y20)
unnamed: J4.14, U1.35 (Y19)
unnamed: J4.15, U1.34 (Y18)
unnamed: J4.16, U1.33 (Y17)
unnamed: J4.17, U1.32 (Y16)
unnamed: J4.18, U1.31 (Y15)
unnamed: J4.19, U1.30 (Y14)
unnamed: J4.20, U1.29 (Y13)
unnamed: J4.21, U1.28 (Y12)
unnamed: J4.22, U1.27 (Y11)
unnamed: J4.23, U1.26 (Y10)
unnamed: J4.24, U1.25 (Y9)
unnamed: J4.25, U1.24 (Y8)
unnamed: J4.26, U1.23 (Y7)
unnamed: J4.27, U1.22 (Y6)
unnamed: J4.28, U1.21 (Y5)
unnamed: J4.29, U1.20 (Y4)
unnamed: J4.30, U1.19 (Y3)
unnamed: J4.31, U1.18 (Y2)
unnamed: J4.32, U1.17 (Y1)

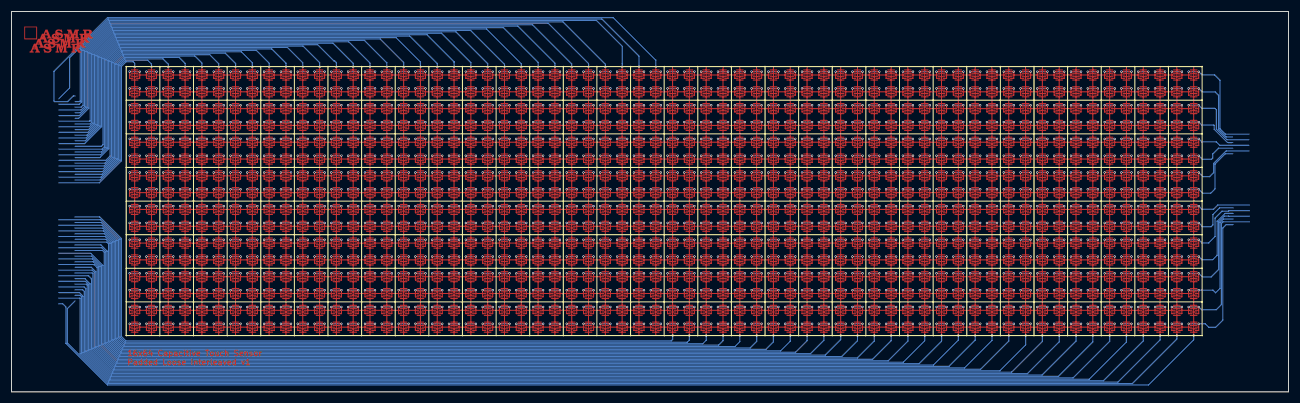
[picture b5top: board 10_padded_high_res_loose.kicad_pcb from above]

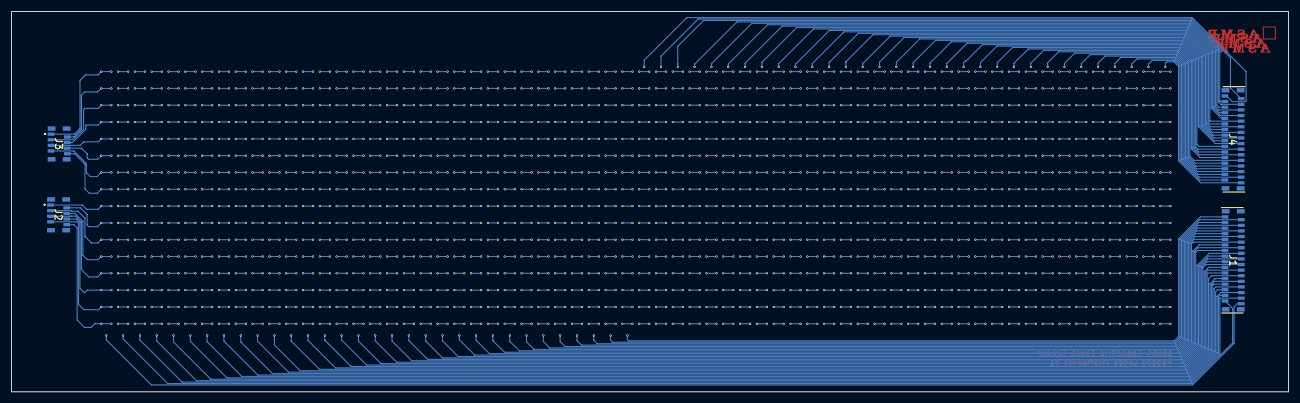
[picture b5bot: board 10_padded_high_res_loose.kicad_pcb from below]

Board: 2 copper layers, 227.9 x 67.9 mm, 5 parts (4 on the bottom side), 80 nets.
